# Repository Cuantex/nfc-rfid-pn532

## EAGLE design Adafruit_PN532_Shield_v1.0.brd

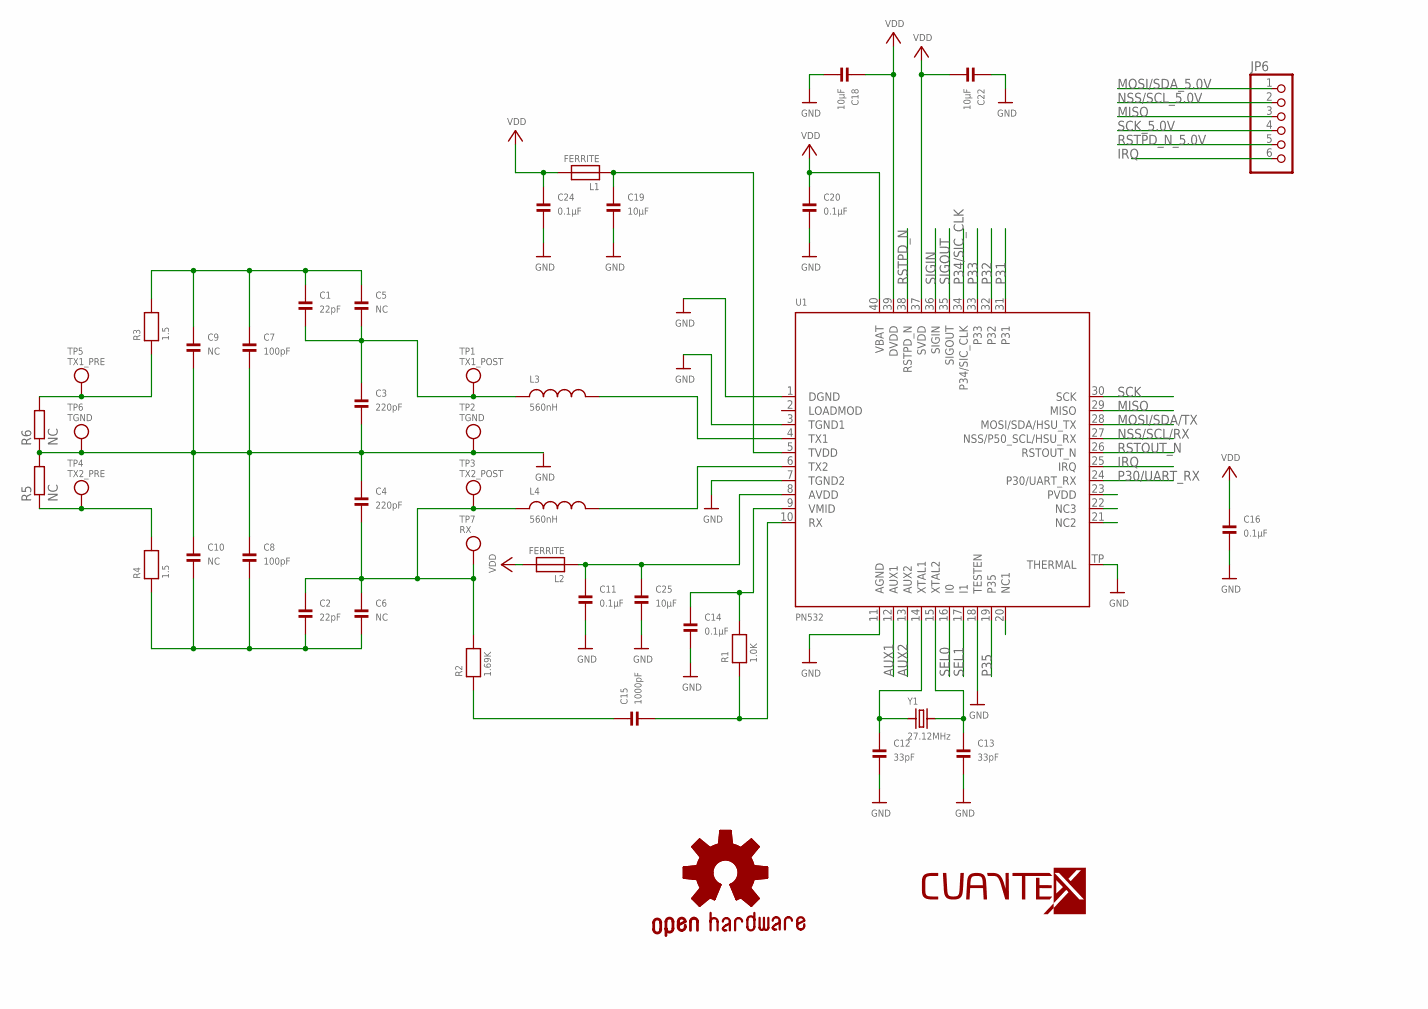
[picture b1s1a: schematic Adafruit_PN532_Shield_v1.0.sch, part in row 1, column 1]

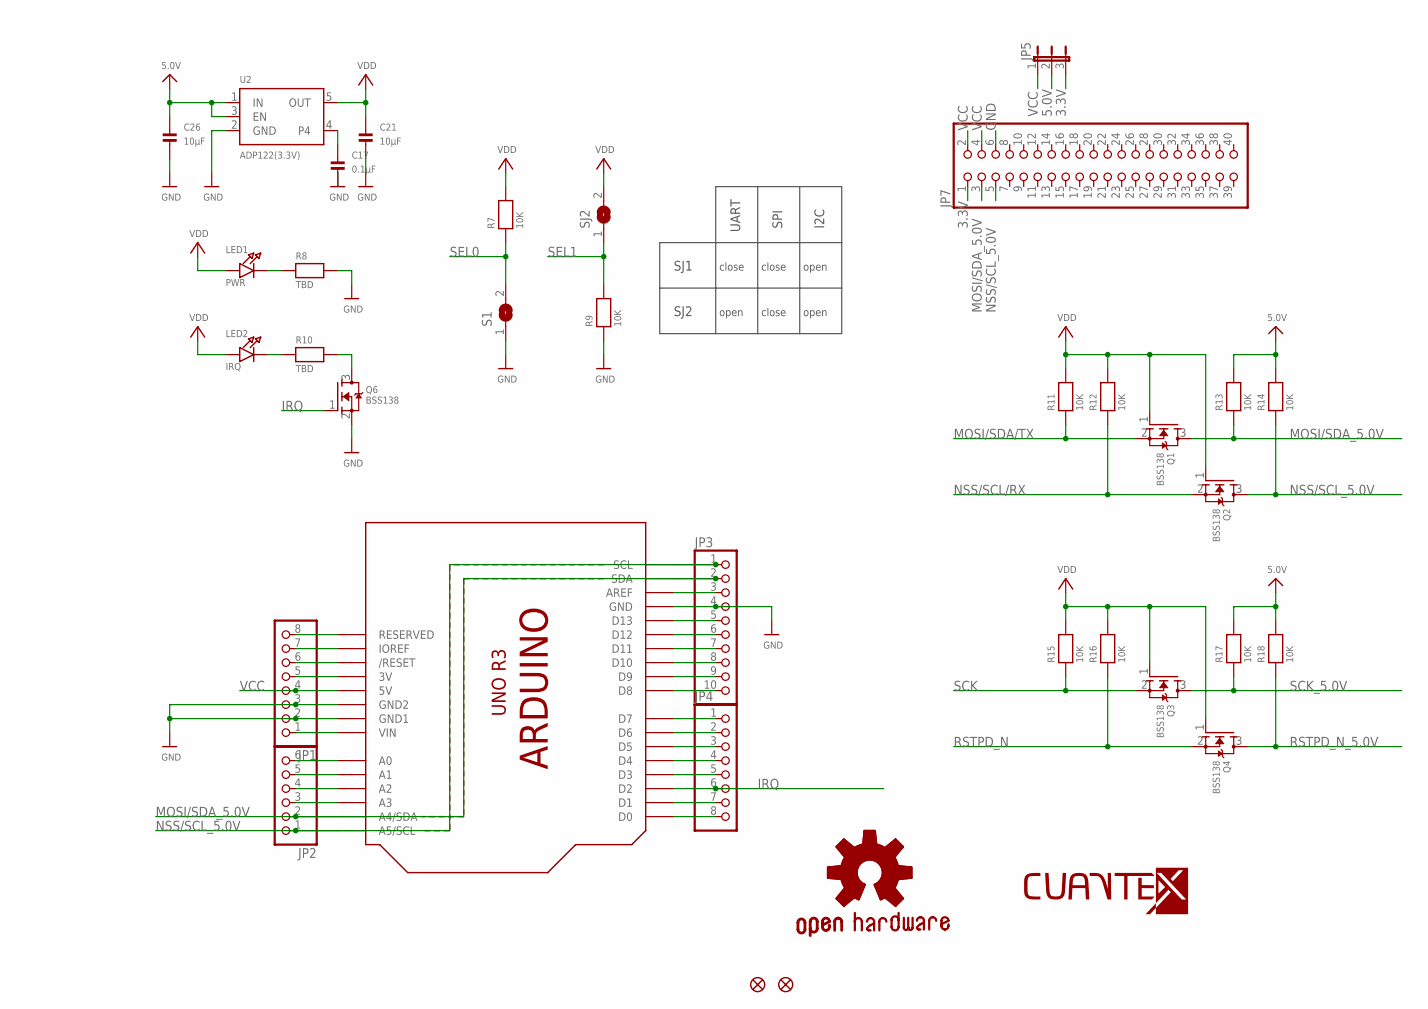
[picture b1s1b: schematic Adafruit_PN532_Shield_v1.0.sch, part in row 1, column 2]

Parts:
C1, C2: 22pF; 0805
C3, C4: 220pF; 0805
C5, C6, C9, C10: NC; 0805
C7, C8: 100pF; 0805
C11, C14, C16, C17, C20, C24: 0.1µF; 0805
C12, C13: 33pF; 0805
C15: 1000pF; 0805
C18, C19, C21, C22, C25, C26: 10µF; 0805
FID1, FID2: FIDUCIAL1X2.5; FIDUCIAL-1X2.5
GOLD_ORB_SM1: OSHWLOGO_GOLD_ORB_SM; OSHW2
GOLD_ORB_SM2: OSHWLOGO_GOLD_ORB_MED; OSHW1
JP1, JP4: HEADER-1X870MIL; 1X08_ROUND_70
JP2: HEADER-1X670MIL; 1X06_ROUND_70
JP3: HEADER-1X1070MIL; 1X10_ROUND70
JP5: JP2E; JP2
JP6: PINHD-1X6B; 1X06-BIG
JP7: PINHD-2X20; 2X20
L1, L2: FERRITE; 0805
L3, L4: 560nH; 0805
LED1: PWR; CHIPLED_0805
LED2: IRQ; CHIPLED_0805
Q1, Q2, Q3, Q4, Q6: BSS138; SOT23-WIDE
R1: 1.0K; 0805
R2: 1.69K; 0805
R3, R4: 1.5; 0805
R5, R6: NC; R0201
R7, R9, R11, R12, R13, R14, R15, R16, R17, R18: 10K; 0805
R8, R10: TBD; 0805
S1: SOLDERJUMPERREFLOW_NOPASTE; SOLDERJUMPER_REFLOW_NOPASTE
SJ2: SOLDERJUMPERREFLOW_NOPASTE; SOLDERJUMPER_REFLOW_NOPASTE
TP1: TX1_POST; TESTPOINT_PAD_2MM
TP2, TP6: TGND; TESTPOINT_PAD_2MM
TP3: TX2_POST; TESTPOINT_PAD_2MM
TP4: TX2_PRE; TESTPOINT_PAD_2MM
TP5: TX1_PRE; TESTPOINT_PAD_2MM
TP7: RX; TESTPOINT_PAD_2MM
U1: PN532; HVQFN40-6X6
U2: ADP122(3.3V); SOT23-5
U3: ARDUINOR3NODIM; ARDUINOR3-NODIM
U$3: LOGO-TOP-50MM; C-3
U$32: LOGO-TOP-100MM; C-8
Y1: 27.12MHz; CRYSTAL_3.2X2.5

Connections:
3.3V: JP1.5, JP5.3, JP7.1, U3.3V
5.0V: C26.1, JP5.2, R13.2, R14.2, R17.2, R18.2, U2.1 (IN), U2.3 (EN)
AUX1: U1.12 (AUX1)
AUX2: U1.13 (AUX2)
GND: C3.2, C4.1, C7.2, C8.1, C9.2, C10.1, C11.2, C12.2, C13.2, C14.2, C16.2, C17.2, C18.2, C19.2, C20.2, C21.2, C22.1, C24.2, C25.2, C26.2, JP1.2, JP1.3, JP3.4, JP7.6, Q6.2 (S), R5.2, R6.1, R8.2, R9.1, S1.1, TP2.P$1, TP6.P$1, U1.1 (DGND), U1.3 (TGND1), U1.7 (TGND2), U1.11 (AGND), U1.18 (TESTEN), U1.TP (THERMAL), U2.2 (GND), U3.GND, U3.GND1, U3.GND2
IRQ: JP4.6, JP6.6, Q6.1 (G), U1.25 (IRQ), U3.D2
MISO: JP6.3, U1.29 (MISO)
MOSI/SDA/TX: Q1.2 (S), R11.1, U1.28 (MOSI/SDA/HSU_TX)
MOSI/SDA_5.0V: JP2.2, JP3.2, JP6.1, JP7.3, Q1.3 (D), R13.1, U3.A4 (A4/SDA), U3.SDA
unnamed: L3.2, U1.4 (TX1)
unnamed: L4.2, U1.6 (TX2)
unnamed: C1.2, C3.1, C5.2, L3.1, TP1.P$1
unnamed: R3.1, R6.2, TP5.P$1
unnamed: R4.2, R5.1, TP4.P$1
unnamed: LED1.C, R8.1
unnamed: C12.1, U1.14 (XTAL1), Y1.1
unnamed: C13.1, U1.15 (XTAL2), Y1.2
unnamed: C15.1, R2.1
unnamed: C14.1, R1.2, U1.9 (VMID)
unnamed: C15.2, R1.1, U1.10 (RX)
unnamed: C2.1, C4.2, C6.1, L4.1, R2.2, TP3.P$1, TP7.P$1
unnamed: C11.1, C25.1, L2.1, U1.8 (AVDD)
unnamed: C19.1, L1.1, U1.5 (TVDD)
unnamed: JP1.1, U3.VIN
unnamed: JP1.6, U3.RESET (/RESET)
unnamed: JP1.7, U3.IOREF
unnamed: JP1.8, U3.RESERVED
unnamed: JP2.3, U3.A3
unnamed: JP2.4, U3.A2
unnamed: JP2.5, U3.A1
unnamed: JP2.6, U3.A0
unnamed: JP3.3, U3.AREF
unnamed: JP3.5, U3.D13
unnamed: JP3.6, U3.D12
unnamed: JP3.7, U3.D11
unnamed: JP3.8, U3.D10
unnamed: JP3.9, U3.D9
unnamed: JP3.10, U3.D8
unnamed: JP4.1, U3.D7
unnamed: JP4.2, U3.D6
unnamed: JP4.3, U3.D5
unnamed: JP4.4, U3.D4
unnamed: JP4.5, U3.D3
unnamed: LED2.C, R10.1
unnamed: JP4.7, U3.D1
unnamed: JP4.8, U3.D0
unnamed: Q6.3 (D), R10.2
unnamed: C17.1, U2.4
NSS/SCL/RX: Q2.2 (S), R12.1, U1.27 (NSS/P50_SCL/HSU_RX)
NSS/SCL_5.0V: JP2.1, JP3.1, JP6.2, JP7.5, Q2.3 (D), R14.1, U3.A5 (A5/SCL), U3.SCL
P30/UART_RX: U1.24 (P30/UART_RX)
P31: U1.31
P32: U1.32
P33: U1.33
P34/SIC_CLK: U1.34 (P34/SIC_CLK)
P35: U1.19 (P35)
RSTOUT_N: U1.26 (RSTOUT_N)
RSTPD_N: Q4.2 (S), R16.1, U1.38 (RSTPD_N)
RSTPD_N_5.0V: JP6.5, Q4.3 (D), R18.1
SCK: Q3.2 (S), R15.1, U1.30 (SCK)
SCK_5.0V: JP6.4, Q3.3 (D), R17.1
SEL0: R7.1, S1.2, U1.16 (I0)
SEL1: R9.2, SJ2.1, U1.17 (I1)
SIGIN: U1.36 (SIGIN)
SIGOUT: U1.35 (SIGOUT)
TX1_ANTENNA: C1.1, C5.1, C7.1, C9.1, R3.2
TX2_ANTENNA: C2.2, C6.2, C8.2, C10.2, R4.1
VCC: JP1.4, JP5.1, JP7.2, JP7.4, U3.5V
VDD: C16.1, C18.1, C20.1, C21.1, C22.2, C24.1, L1.2, L2.2, LED1.A, LED2.A, Q1.1 (G), Q2.1 (G), Q3.1 (G), Q4.1 (G), R7.2, R11.2, R12.2, R15.2, R16.2, SJ2.2, U1.37 (SVDD), U1.39 (DVDD), U1.40 (VBAT), U2.5 (OUT)

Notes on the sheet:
SJ1
SJ2
UART
SPI
I2C
close
open

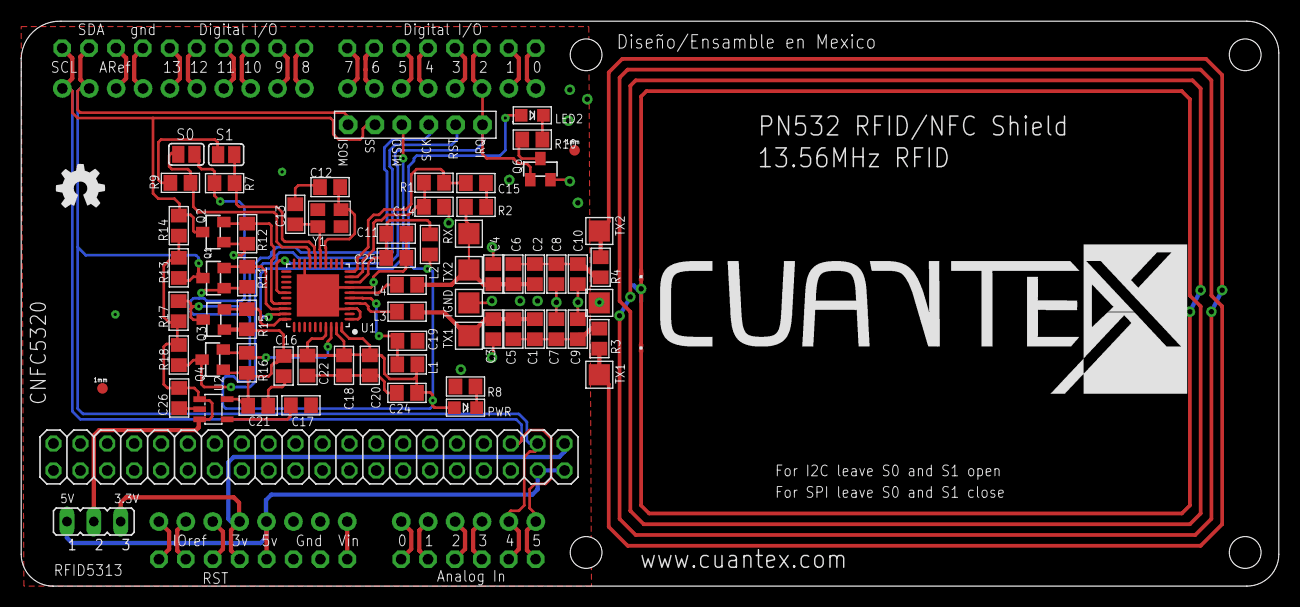
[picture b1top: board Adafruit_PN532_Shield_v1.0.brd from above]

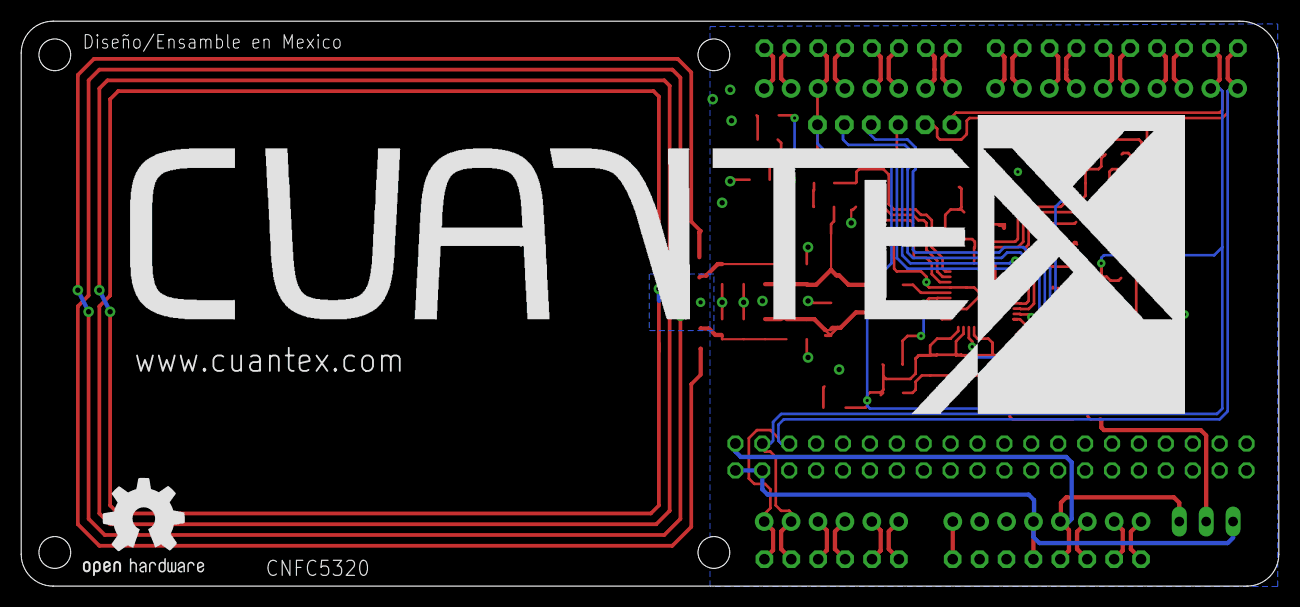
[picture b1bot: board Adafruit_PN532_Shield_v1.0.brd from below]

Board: 2 copper layers, 118.7 x 53.3 mm, 80 parts (2 on the bottom side), 58 nets.

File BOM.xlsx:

Qty | Value | Device | Package | Parts | Description
1 | NC | HEADER-1X1070MIL | 1X10_ROUND70 | JP3 | DO NOT PLACE | NC
1 | NC | HEADER-1X670MIL | 1X06_ROUND_70 | JP2 | DO NOT PLACE | NC
2 | NC | HEADER-1X870MIL | 1X08_ROUND_70 | JP1, JP4 | DO NOT PLACE | NC
1 | NC | JP2E | JP2 | JP5 | DO NOT PLACE | NC
1 | NC | PINHD-1X6B | 1X06-BIG | JP6 | DO NOT PLACE | NC
1 | NC | PINHD-2X20 | 2X20 | JP7 | DO NOT PLACE | NC
6 | 0.1µF | CAP_CERAMIC0805 | 805 | C11, C14, C16, C17, C20, C24 | Ceramic Capacitors
1 | 1.0K | RESISTOR0805 | 805 | R1 | Resistors
2 | 1.5k | RESISTOR0805 | 805 | R3, R4 | Resistors
1 | 1.69K | RESISTOR0805 | 805 | R2 | Resistors
1 | 1000pF | CAP_CERAMIC0805 | 805 | C15 | Ceramic Capacitors
2 | 100pF | CAP_CERAMIC0805 | 805 | C7, C8 | Ceramic Capacitors
10 | 10K | RESISTOR0805 | 805 | R7, R9, R11, R12, R13, R14, R15, R16, R17, R18 | Resistors
6 | 10µF | CAP_CERAMIC0805 | 805 | C18, C19, C21, C22, C25, C26 | Ceramic Capacitors
2 | 220pF | CAP_CERAMIC0805 | 805 | C3, C4 | Ceramic Capacitors
2 | 22pF | CAP_CERAMIC0805 | 805 | C1, C2 | Ceramic Capacitors
1 | 27.12MHz | CRYSTALTHIN | CRYSTAL_3.2X2.5 | Y1 | Crystals
2 | 33pF | CAP_CERAMIC0805 | 805 | C12, C13 | Ceramic Capacitors
2 | 560nH | INDUCTOR0805 | 805 | L3, L4 | Inductors
1 | ADP122(3.3V) | VREG_SOT23-5 | SOT23-5 | U2 | SOT23-5 Fixed Voltage Regulators
1 | ARDUINOR3NODIM | ARDUINOR3NODIM | ARDUINOR3-NODIM | U3 | This is a new object for the new Arduino R3 - with extra pins that you may want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
5 | BSS138 | MOSFET-NWIDE | SOT23-WIDE | Q1, Q2, Q3, Q4, Q6 | N-Channel Mosfet
2 | FERRITE | FERRITE0805 | 805 | L1, L2 | Ferrite Bead
1 | IRQ | LED0805 | CHIPLED_0805 | LED2 | LED
4 | NC | CAP_CERAMIC0805 | 805 | C5, C6, C9, C10 | Ceramic Capacitors | NC
2 | NC | R-EU_R0201 | R0201 | R5, R6 | RESISTOR, European symbol | NC
1 | PN532 | PN532 | HVQFN40-6X6 | U1 | PN532 - Near Field Communication (NFC) controller
1 | PWR | LED0805 | CHIPLED_0805 | LED1 | LED
2 | TBD | RESISTOR0805 | 805 | R8, R10 | Resistors

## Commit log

2016-03-28 Archivos en Git
